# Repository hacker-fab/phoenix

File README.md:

# phoenix

Phoenix is a tube furnace used for thermal oxidation and annealing.

It uses PID control to follow custom temperature profiles and works on both MicroPython on the ESP32 and a simulated Python desktop environment.

<table>
  <tr>
    <td>
      <br>
      <sub>Fig 1. Tube furnace in action</sub>
    </td>
    <td>
      <br>
      <sub>Fig 2. Simulated PID following a heat profile</sub>
    </td>
    <td>
      <br>
      <sub>Fig 3. Controlling ramp rate to prevent thermal shock</sub>
    </td>
  </tr>
</table>

# Python setup
```bash
python3 -m venv .venv
source .venv/bin/activate
pip install -r requirements.txt
```

# Micropython setup

Install micropython
```bash
https://github.com/micropython/micropython/tree/master/ports/unix#readme
```

Install `typing`
```bash
micropython -m mip install github:josverl/micropython-stubs/mip/typing.mpy
```

Install `udataclasses`
```bash
cd ~/.micropython/lib
# extract src/udataclasses
git clone https://github.com/dhrosa/udataclasses.git tmp
mv tmp/src/udataclasses .
rm -rf tmp
```

# Flash code
```
esptool erase-flash
esptool --baud 460800 write-flash 0 images/ESP32_GENERIC_S3-SPIRAM_OCT-20250809-v1.26.0.bin

mpremote
mpremote connect /dev/ttyUSB0 fs cp main.py :
```
- use the UART port (left side) for flashing
- use the USB port (right side) when using mpremote

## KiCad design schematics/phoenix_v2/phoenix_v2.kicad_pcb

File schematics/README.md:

Reverse engineered schematic based on the code from ProjectsInFlight

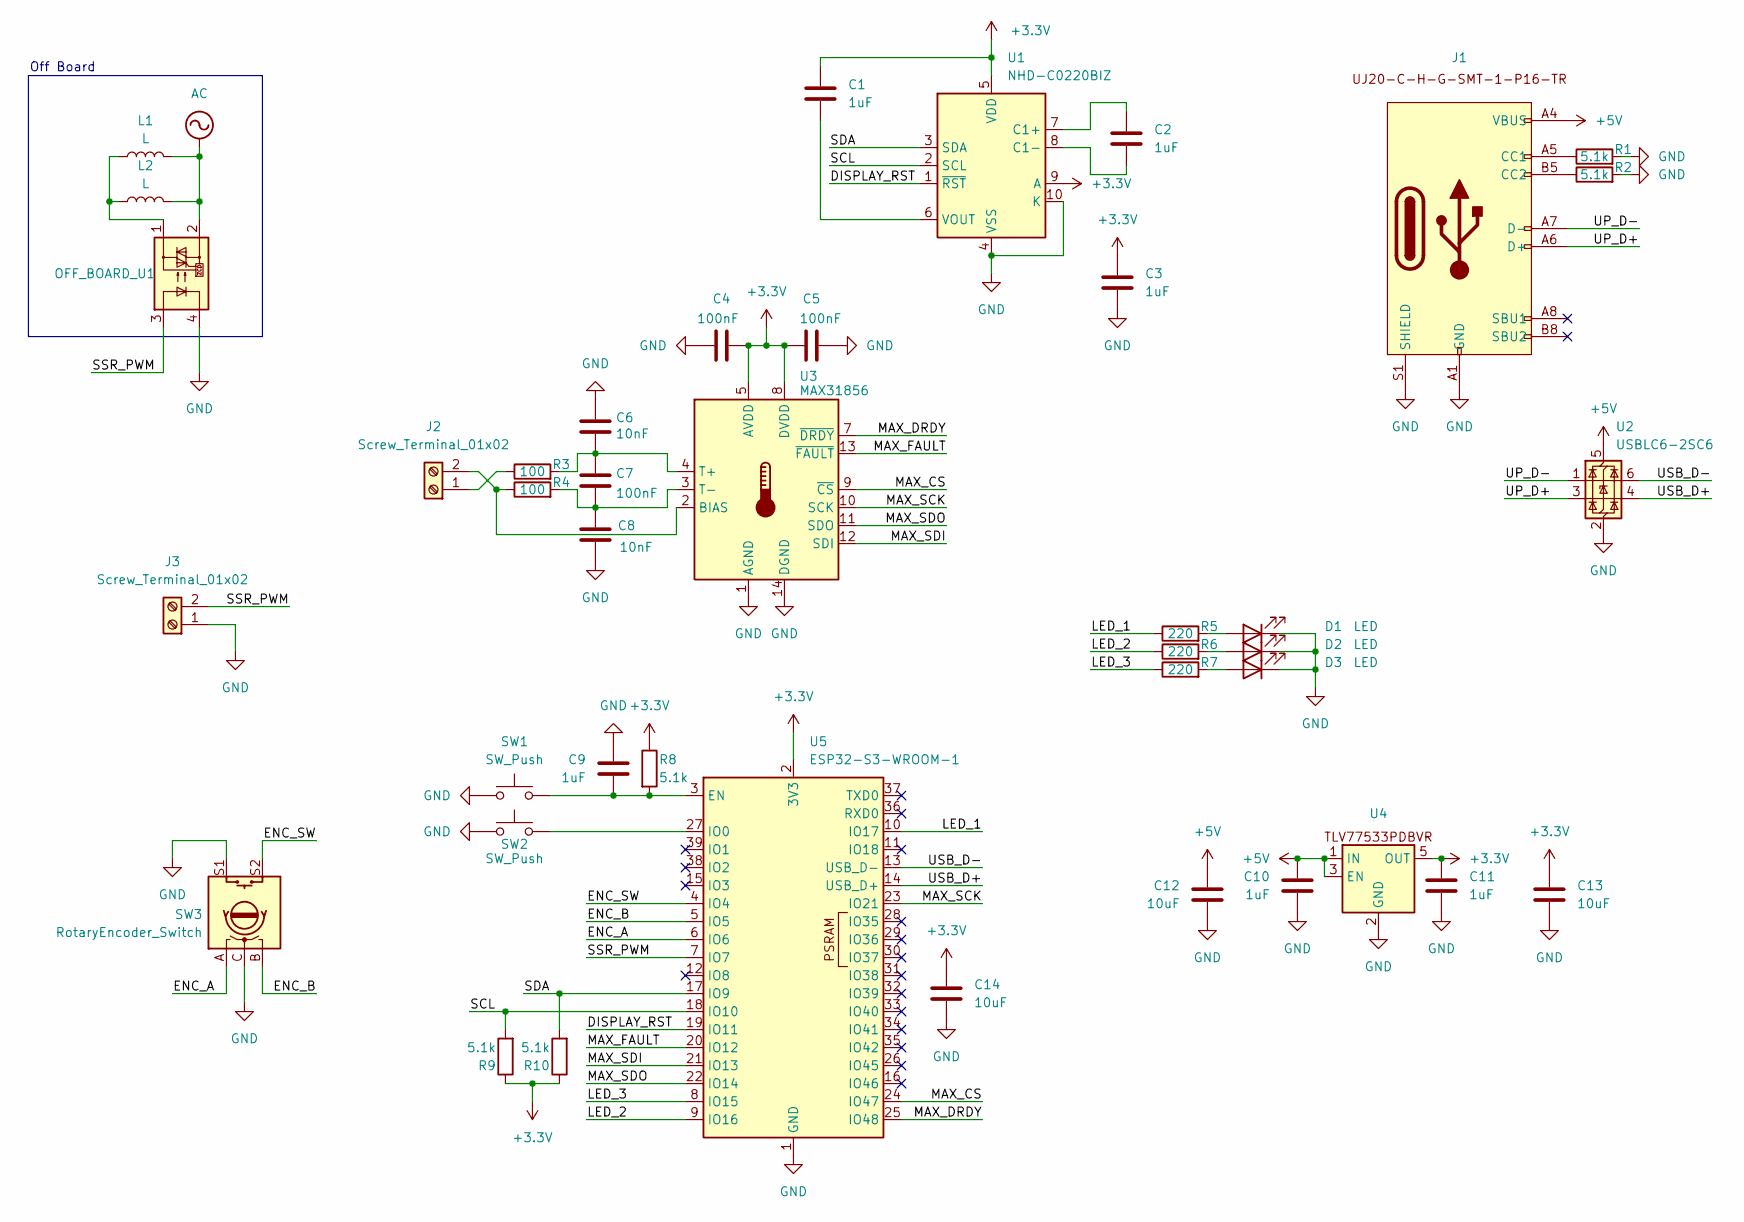
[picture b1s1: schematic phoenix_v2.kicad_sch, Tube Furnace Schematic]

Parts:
C1, C2, C3, C9, C10, C11: 1uF; C_0805_2012Metric
C4, C5, C7: 100nF; C_0805_2012Metric
C6, C8: 10nF; C_0805_2012Metric
C12, C13, C14: 10uF; C_1206_3216Metric_Pad1.33x1.80mm_HandSolder
D1, D2, D3: LED; D_0805_2012Metric_Pad1.15x1.40mm_HandSolder
J1: UJ20-C-H-G-SMT-1-P16-TR
J2, J3: Screw_Terminal_01x02; TE_282837-2
L1, L2: L
OFF_BOARD_U1: (no value)
R1, R2, R8, R9, R10: 5.1k; R_0805_2012Metric_Pad1.20x1.40mm_HandSolder
R3, R4: 100; R_0805_2012Metric_Pad1.20x1.40mm_HandSolder
R5, R6, R7: 220; R_0805_2012Metric_Pad1.20x1.40mm_HandSolder
SW1, SW2: SW_Push; SW_TH_Tactile_Omron_B3F-102x
SW3: RotaryEncoder_Switch; PEC164120FS0012
U1: NHD-C0220BIZ; NHD-C0220BiZ
U2: USBLC6-2SC6; SOT-23-6
U3: MAX31856; TSSOP-14_4.4x5mm_P0.65mm
U4: SOT-23-5
U5: ESP32-S3-WROOM-1

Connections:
+3.3V: C1.1, C3.1, C4.2, C5.1, C11.1, C13.1, C14.1, R8.1, R9.1, R10.1, U1.5 (VDD), U1.9 (A), U3.5 (AVDD), U3.8 (DVDD), U4.5 (OUT), U5.2 (3V3)
+5V: C10.1, C12.1, J1.A4 (VBUS), J1.A9 (VBUS), J1.B4 (VBUS), J1.B9 (VBUS), U2.5 (VBUS), U4.1 (IN), U4.3 (EN)
/DISPLAY_RST: U1.1 (~RST), U5.19 (IO11)
/ENC_A: SW3.A, U5.6 (IO6)
/ENC_B: SW3.B, U5.5 (IO5)
/ENC_SW: SW3.S2, U5.4 (IO4)
/LED_1: R5.1, U5.10 (IO17)
/LED_2: R6.1, U5.9 (IO16)
/LED_3: R7.1, U5.8 (IO15)
/MAX_CS: U3.9 (~CS), U5.24 (IO47)
/MAX_DRDY: U3.7 (~DRDY), U5.25 (IO48)
/MAX_FAULT: U3.13 (~FAULT), U5.20 (IO12)
/MAX_SCK: U3.10 (SCK), U5.23 (IO21)
/MAX_SDI: U3.12 (SDI), U5.21 (IO13)
/MAX_SDO: U3.11 (SDO), U5.22 (IO14)
/SCL: R9.2, U1.2 (SCL), U5.18 (IO10)
/SDA: R10.2, U1.3 (SDA), U5.17 (IO9)
/SSR_PWM: J3.2, OFF_BOARD_U1.3, U5.7 (IO7)
/UP_D+: J1.A6 (D+), J1.B6 (D+), U2.3 (I/O2)
/UP_D-: J1.A7 (D-), J1.B7 (D-), U2.1 (I/O1)
/USB_D+: U2.4 (I/O2), U5.14 (USB_D+)
/USB_D-: U2.6 (I/O1), U5.13 (USB_D-)
GND: C3.2, C4.1, C5.2, C6.1, C8.2, C9.1, C10.2, C11.2, C12.2, C13.2, C14.2, D1.1 (K), D2.1 (K), D3.1 (K), J1.A1 (GND), J1.A12 (GND), J1.B1 (GND), J1.B12 (GND), J1.S1 (SHIELD), J3.1, OFF_BOARD_U1.4, R1.2, R2.2, SW1.1, SW2.1, SW3.C, SW3.S1, U1.4 (VSS), U1.10 (K), U2.2 (GND), U3.1 (AGND), U3.14 (DGND), U4.2 (GND), U4.4 (NC), U5.1 (GND), U5.40 (GND), U5.41 (GND)
unnamed: D1.2 (A), R5.2
unnamed: D2.2 (A), R6.2
unnamed: D3.2 (A), R7.2
unnamed: J1.A5 (CC1), R1.1
unnamed: J1.B5 (CC2), R2.1
unnamed: J2.1, R3.1
unnamed: J2.2, R4.1, U3.2 (BIAS)
unnamed: L1.1, L2.1, OFF_BOARD_U1.1
unnamed: L1.2, L2.2, OFF_BOARD_U1.2
unnamed: C2.1, U1.7 (C1+)
unnamed: C2.2, U1.8 (C1-)
unnamed: C1.2, U1.6 (VOUT)
unnamed: C6.2, C7.1, R3.2, U3.4 (T+)
unnamed: C7.2, C8.1, R4.2, U3.3 (T-)
unnamed: C9.2, R8.2, SW1.2, U5.3 (EN)
unnamed: SW2.2, U5.27 (IO0)

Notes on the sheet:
Off Board

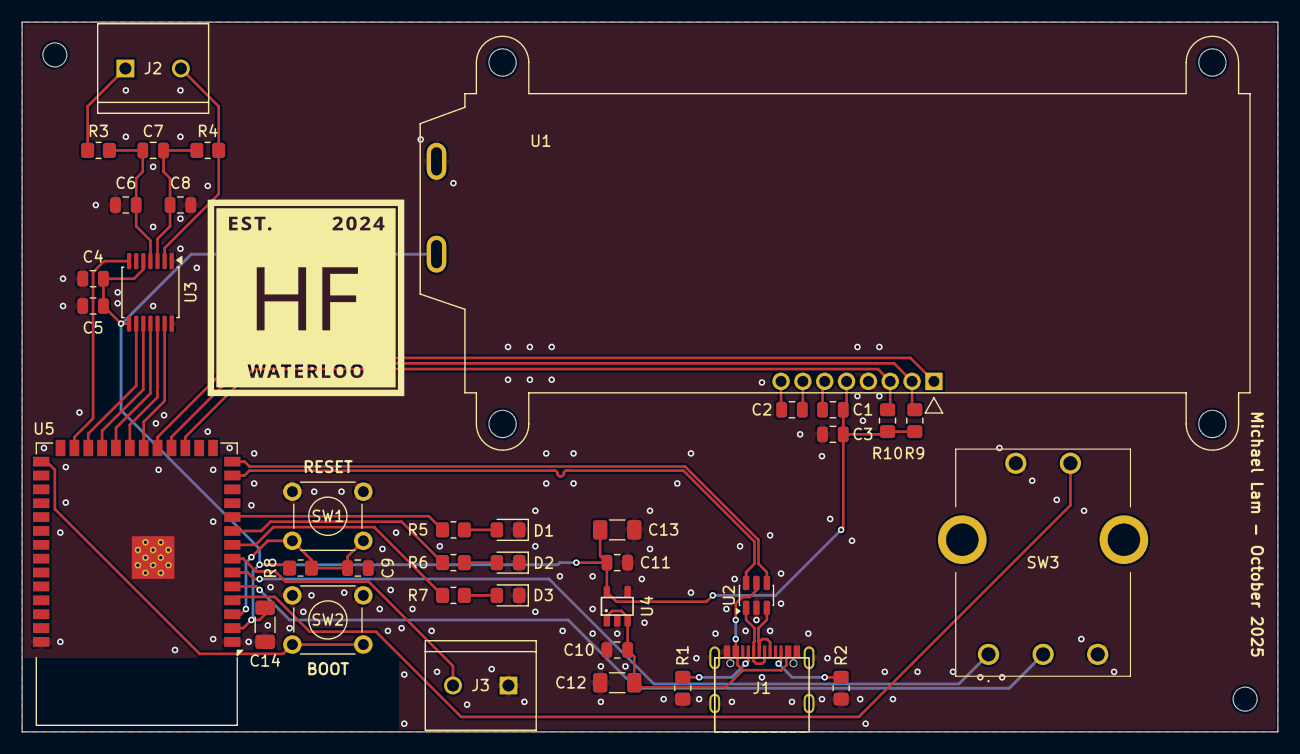
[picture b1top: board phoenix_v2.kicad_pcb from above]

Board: 2 copper layers, 115.0 x 65.0 mm, 38 parts (0 on the bottom side), 37 nets.

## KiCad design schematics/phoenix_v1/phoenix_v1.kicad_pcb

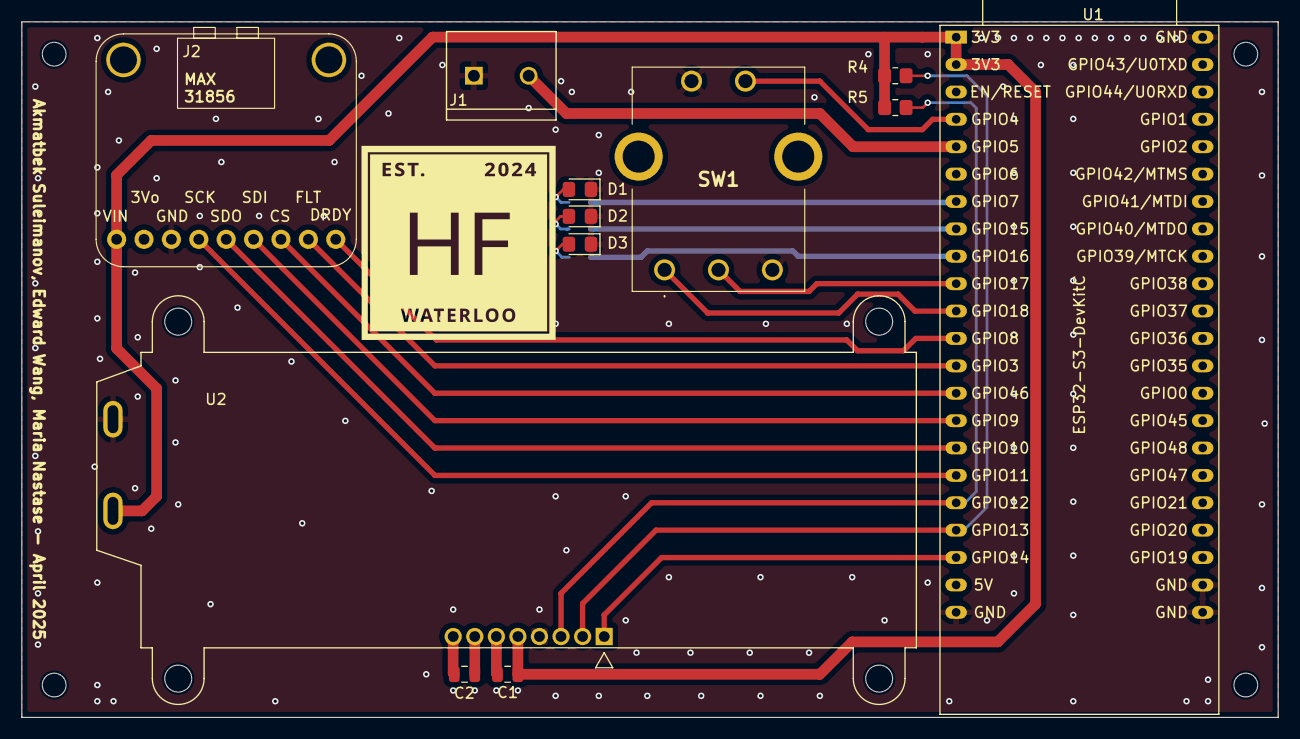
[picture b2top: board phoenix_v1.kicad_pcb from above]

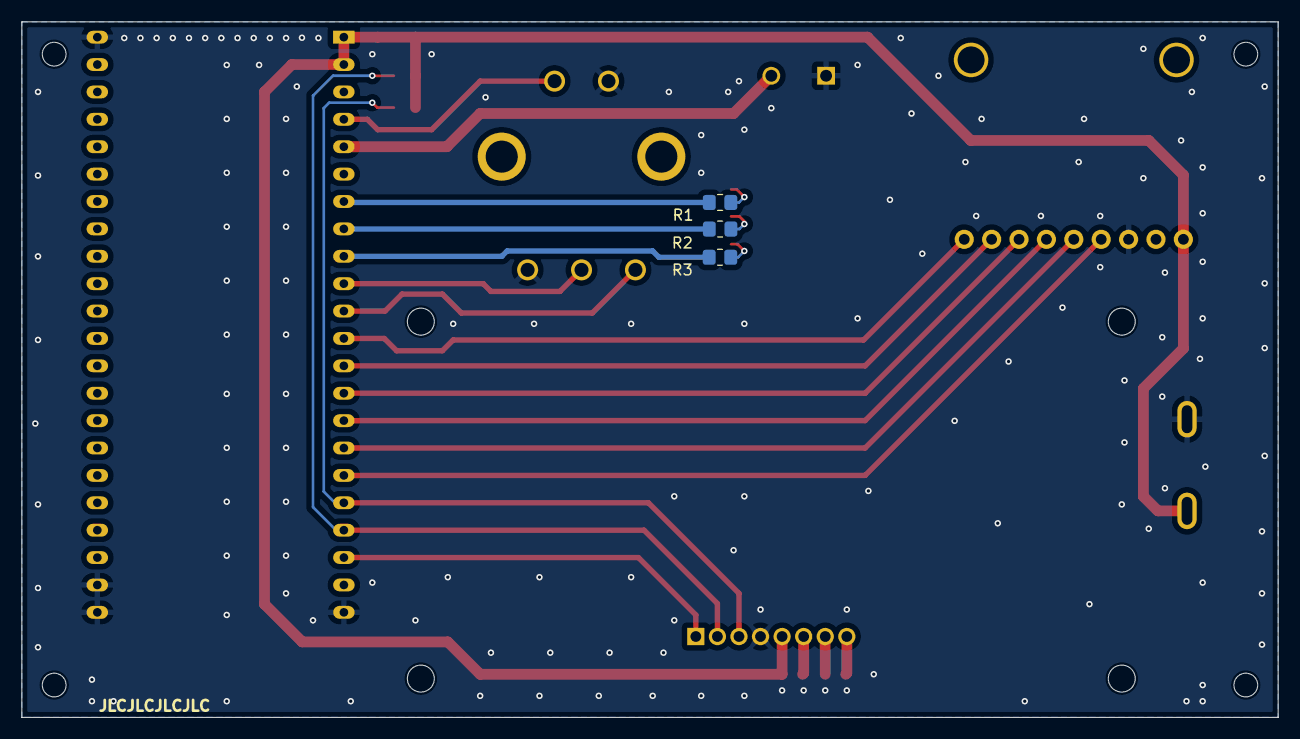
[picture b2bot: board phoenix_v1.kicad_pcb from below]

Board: 2 copper layers, 116.5 x 64.5 mm, 15 parts (3 on the bottom side), 24 nets.

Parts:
C1, C2: 1uF; C_0805_2012Metric
D1, D2, D3: LED; D_0805_2012Metric_Pad1.15x1.40mm_HandSolder
J1: Screw_Terminal_01x02; TE_282837-2
J2: Conn_01x09_Socket; MAX31856_HEADER
R1, R2, R3: 220; R_0805_2012Metric_Pad1.20x1.40mm_HandSolder
R4, R5: 4.7k; R_0805_2012Metric_Pad1.20x1.40mm_HandSolder
SW1: RotaryEncoder_Switch; PEC164120FS0012
U1: ESP32-S3-DevKitC
U2: NHD-C0220BIZ; NHD-C0220BiZ

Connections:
+3.3V: C1.1, J2.9, R4.1, R5.1, U1.1 (3V3), U1.2 (3V3), U2.5 (VDD), U2.9 (A)
/DISPLAY_RST: U1.20 (GPIO14/ADC2_CH3), U2.1 (~RST)
/ENC_A: SW1.A, U1.11 (GPIO18/ADC2_CH7)
/ENC_B: SW1.B, U1.10 (GPIO17/ADC2_CH6)
/ENC_SW: SW1.S2, U1.4 (GPIO4/ADC1_CH3)
/LED_1: R1.1, U1.7 (GPIO7/ADC1_CH6)
/LED_2: R2.1, U1.8 (GPIO15/ADC2_CH4/32K_P)
/LED_3: R3.1, U1.9 (GPIO16/ADC2_CH5/32K_N)
/MAX_CS: J2.3, U1.14 (GPIO46)
/MAX_DRDY: J2.1, U1.12 (GPIO8/ADC1_CH7)
/MAX_FAULT: J2.2, U1.13 (GPIO3/ADC1_CH2)
/MAX_SCK: J2.6, U1.17 (GPIO11/ADC2_CH0)
/MAX_SDI: J2.4, U1.15 (GPIO9/ADC1_CH8)
/MAX_SDO: J2.5, U1.16 (GPIO10/ADC1_CH9)
/SCL: R4.2, U1.19 (GPIO13/ADC2_CH2), U2.2 (SCL)
/SDA: R5.2, U1.18 (GPIO12/ADC2_CH1), U2.3 (SDA)
/SSR_PWM: J1.2, U1.5 (GPIO5/ADC1_CH4)
GND: D1.1 (K), D2.1 (K), D3.1 (K), J1.1, J2.7, SW1.C, SW1.S1, U1.22 (GND), U1.23 (GND), U1.24 (GND), U1.44 (GND), U2.4 (VSS), U2.10 (K)
unnamed: D1.2 (A), R1.2
unnamed: D2.2 (A), R2.2
unnamed: D3.2 (A), R3.2
unnamed: C2.1, U2.7 (C1+)
unnamed: C2.2, U2.8 (C1-)
unnamed: C1.2, U2.6 (VOUT)

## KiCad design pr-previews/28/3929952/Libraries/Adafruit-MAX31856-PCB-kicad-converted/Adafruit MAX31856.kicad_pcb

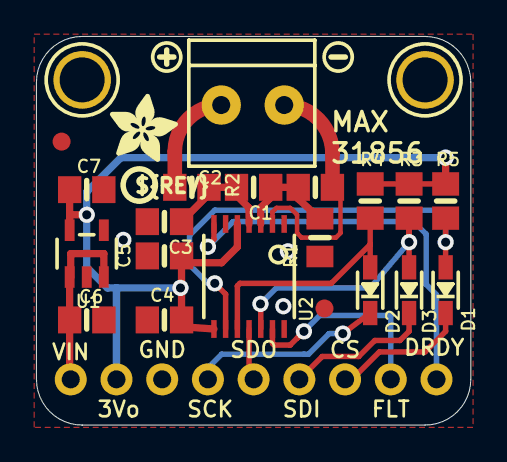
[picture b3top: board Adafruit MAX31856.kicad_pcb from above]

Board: 2 copper layers, 24.1 x 21.6 mm, 28 parts (1 on the bottom side), 16 nets.

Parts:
C1: 0.01uF; 0805_10MGAP
C2, C4, C5: 0.1uF; 0805-NO
C3: 0.01uF; 0805-NO
C6, C7: 10uF; 0805-NO
D1, D2, D3: 1N4148; SOD-323
FID1, FID2: FIDUCIAL""; FIDUCIAL_1MM
JP1: 1X09_ROUND_70
R1, R2: 100; 0805-NO
R3, R4, R5: 10K; 0805-NO
U1: mic5225-3.3; SOT23-5
U2: MAX31856; TSSOP14
U$1: PCBFEAT-REV-040
U$13, U$14: MOUNTINGHOLE2.5; MOUNTINGHOLE_2.5_PLATED
U$23: SYMBOL_PLUS
U$24: SYMBOL_MINUS
U$25: ADAFRUIT_3.5MM
U$26: ADAFRUIT_TEXT_20MM
X1: 3.5mm term; TERMBLOCK_1X2-3.5MM

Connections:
3.3V: C4.1, C5.1, C7.1, JP1.8, R3.2, R4.2, R5.2, U1.5, U2.5, U2.8
DRDY: JP1.1, U2.7
GND: C1.1, C3.2, C4.2, C5.2, C6.2, C7.2, JP1.7, U1.2, U2.1, U2.14
SCK: D2.C, JP1.6
SCK_3V: D2.A, R4.1, U2.10
SDI: D3.C, JP1.4
SDO: JP1.5, U2.11
SDO_3V: D3.A, R3.1, U2.12
T+: C2.2, C3.1, R2.2, U2.4
T-: C1.2, C2.1, R1.2, U2.3
THERM+: R2.1, X1.1
THERM-: R1.1, U2.2, X1.2
VIN: C6.1, JP1.9, U1.1, U1.3
~CS_3V: D1.A, R5.1, U2.9
~CS: D1.C, JP1.3
~FAULT: JP1.2, U2.13

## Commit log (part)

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2025-02-05 upload
2025-02-05 rename src -> TubeFurnace
2025-02-05 installation guide
2025-02-05 formatting
2025-02-05 Revert "formatting"
    This reverts commit 083058cc252f3819b7a6246fb17b9b03613ff680.
2025-02-05 Update LICENSE
2025-02-05 test
2025-02-05 matrix and ls
2025-02-05 fix path
2025-02-05 fix path 2
2025-02-05 install avr
2025-02-05 update index
2025-02-05 cleanup chatgpt comments
2025-02-05 cleanup job name
2025-02-05 build in ci (#3)
    * test
    * matrix and ls
    * fix path
    * fix path 2
    * install avr
    * update index
2025-02-05 .clang-format
2025-02-05 autoformat
2025-02-05 run in ci
2025-02-05 Revert "run in ci"
    This reverts commit 9e731130f4431728779fc97e86db32f08336ba59.
2025-02-05 don't redeclare injected function headers
2025-02-05 autoformat (#4)
    * .clang-format
    * autoformat
    * run in ci
    * Revert "run in ci"
    This reverts commit 9e731130f4431728779fc97e86db32f08336ba59.
    * don't redeclare injected function headers
2025-02-05 lint job
2025-02-05 only needs to run on ubuntu
2025-02-05 linter (#5)
    * run in ci
    * lint job
    * only needs to run on ubuntu
2025-02-05 update readme (#6)
2025-02-05 make linter able to fail
2025-02-05 test with bad indentation
2025-02-05 Revert "test with bad indentation"
    This reverts commit 8122fc583a4bc7f4e7ee4da30116c309f4d25178.
2025-02-05 make linter able to fail (#9)
    * make linter able to fail
    * test with bad indentation
    * Revert "test with bad indentation"
    This reverts commit 8122fc583a4bc7f4e7ee4da30116c309f4d25178.
2025-02-08 move tests to seperate folders
2025-02-08 move tests to seperate folders (#10)
2025-02-08 move tests to root
2025-02-27 relay test script
2025-02-27 relay test script (#12)
2025-02-27 gitignore
2025-02-27 rename to v0
2025-02-27 rename kicad project to v0 (#13)
    * gitignore
    * rename to v0
2025-03-01 add esp32 libraries
2025-03-07 v1 schematic
2025-03-08 update for esp32
2025-03-08 screw terminal
2025-03-08 comment
2025-03-08 update test_thermocouple for esp32 (#16)
    * update for esp32
    * comment
2025-03-10 update screnshot
2025-03-10 v1 schematic (#14)
    * v1 schematic
    * screw terminal
    * update screnshot
    ---------
2025-03-10 layout
2025-03-10 fix duplicate
2025-03-10 max31856 socket
2025-03-11 add ncs
2025-03-17 upload screw terminal files
2025-03-17 footprint assignment
2025-03-17 upload MAX31856 eagle-converted source
2025-03-17 create custom footprint for MAX31856 header
2025-03-19 upload pec stuff
2025-03-19 use project footprint library
2025-03-21 extract PEC footprint and sym
2025-03-21 finish assigning footprints and update PCB
2025-03-21 assign footprints (#17)
    * layout
    * fix duplicate
    * max31856 socket
    * add ncs
    * upload screw terminal files
    * footprint assignment
2025-03-21 exclude relay and inductors from board
2025-03-21 exclude relay and inductors from board (#18)
2025-03-21 set R for leds
2025-03-21 set R for leds (#19)
2025-03-21 reannotate
2025-03-21 reannotate (#20)
2025-03-21 caps for display (#21)
2025-03-21 first try
2025-03-21 upload pages v3
2025-03-21 better title
2025-03-21 try kiri instead
2025-03-21 checkout v4?
2025-03-21 reddragon version
2025-03-21 try branch
2025-03-21 use fork with upload v4
2025-03-21 random diff to trigger run
2025-03-21 try overall checkout v2
2025-03-21 go back
2025-03-21 initial nojekyll
2025-03-21 retrigger
2025-03-21 correct .kicad_pro path
2025-03-21 v1.2
2025-03-21 random edit to trigger
2025-03-21 make a .kiri folder and trigger
2025-03-21 more trigger
2025-03-21 perms
2025-03-21 Update Kiri output for PR #23
2025-03-21 pr perm
2025-03-21 try gitkeep?
2025-03-21 try different path and pwd
2025-03-21 USE THE ENV VAR CORRECTLY!!!!!!!!!!!
2025-03-21 revert sch
2025-03-21 v1.2.1
2025-03-21 v1.2.2
2025-03-21 v.1.2.3
2025-03-21 v.1.2.4
2025-03-21 kiri setup (#23)
    * first try
    * upload pages v3
    * better title
    * try kiri instead
    * checkout v4?
    * reddragon version
2025-03-21 trigger
2025-03-21 output dir
2025-03-21 try fix output dir
2025-03-21 no output dir
2025-03-21 v.1.2.5
2025-03-21 v.1.2.6
2025-03-21 v.1.2.7
2025-03-21 v1.2.8
2025-03-21 v1.2.9
2025-03-21 v1.2.10
2025-03-21 v1.2.11
2025-03-21 v1.2.12
2025-03-21 revert move
2025-03-21 Revert "revert move"
    This reverts commit c8a7fecc3ba229a40b8fc048a70462a0a6fe9e72.
2025-03-21 Revert "Revert "revert move""
    This reverts commit a785919d6cb81062de9690204b0b46e338bb406e.
2025-03-21 v.1.2.13
2025-03-21 v1.2.14
2025-03-21 Revert "Revert "Revert "revert move"""
    This reverts commit 077da6f8a26816faf5dd7f152d1a63141e9c7252.
2025-03-21 github-pages env
2025-03-21 Revert "Revert "Revert "Revert "revert move""""
    This reverts commit 9c1976028def966c5564fcd19b8b1fd2f330ae00.
2025-03-21 v1.2.15
2025-03-21 Revert "Revert "Revert "Revert "Revert "revert move"""""
    This reverts commit ef8d35f938a2ff7061ca819bc9f4d280fc4012b7.
2025-03-21 v1.2.17
2025-03-21 v1.2.18
2025-03-21 Revert "Revert "Revert "Revert "Revert "Revert "revert move""""""
    This reverts commit e7fcf7812303bad959b3ae7c36b8afc2bb990449.
2025-03-21 Revert "Revert "Revert "Revert "Revert "Revert "Revert "revert move"""""""
    This reverts commit 42d8571e8d9c44e463d96eba7e5713493cb319a8.
2025-03-22 show which direction MAX is facing
2025-03-22 arrange and draw outline
2025-03-22 Update Kiri output for PR #25
2025-03-22 better alignment
2025-03-22 arrange stuff and draw outline (#25)
    * show which direction MAX is facing
    * arrange and draw outline
    * better alignment
    ---------
2025-03-22 fix encoder footprint and label mismatch
2025-03-22 Update Kiri output for PR #26
2025-03-22 update on pcb
2025-03-22 fix max footprint (#27)
    * delete extra stuff on max breakout footprint
    * update on pcb
    ---------
2025-03-22 make board outline silkscreen instead of edgecuts
2025-03-22 some wiring
2025-03-22 update pcb for max footprint
2025-03-22 cleanup max header
2025-03-22 route everything and GND fill and via stitch
2025-03-22 Update Kiri output for PR #28
2025-03-26 v2.0.2
2025-03-26 tiny change to trigger diff
2025-03-26 environment: github pages
2025-03-26 another small diff
2025-03-26 v2.0.3
2025-03-26 v2.0.4
2025-03-26 v2.0.5
2025-03-26 Update Kiri output for PR #29
2025-03-26 kiri action on gh-pages classic (#29)
    * v2.0.2
    * tiny change to trigger diff
    * environment: github pages
    * another small diff
    * v2.0.3
    * v2.0.4
2025-03-26 title blocks
2025-03-26 export pdfs
2025-04-12 fix "Dont mix global and local net labels for the same net (SSR_PWM)"
2025-04-12 fix "it should be made clear on the schematic that U1 and surrounding components are off board"
2025-04-12 fix "NHD-CO22BIZ needs 3.3V not 5V"
2025-04-12 connect A and K on lcd
2025-04-12 fix "routing for the I2C pullups VDD trace"
2025-04-12 fix "more space on display mounting holes"
2025-04-12 upload DRU
2025-04-12 fix new DRC errors
2025-04-12 more vias
2025-04-12 zip gerber script
2025-04-12 generate GERB
2025-04-12 update zip script for new path
2025-04-13 HF log!!!!!!!!
2025-04-13 hf logo as footprint
2025-04-13 update gerb
2025-04-13 add names and mounting holes
2025-04-13 fix J1 missing
2025-04-15 routing (#28)
    * make board outline silkscreen instead of edgecuts
    * some wiring
    * update pcb for max footprint
    * cleanup max header
    * route everything and GND fill and via stitch
    * title blocks
2025-04-16 requirements
2025-04-16 chat... gpt...
2025-04-16 improvement
2025-04-16 python gitignore
2025-04-16 req.txt
2025-04-16 split out running_average
2025-04-16 test_running_average.py
2025-04-16 split out pid.py and sim.py
2025-04-16 rename RampSoakPID -> RampSoak
2025-04-16 rename HeatSimConfig -> ThermalModel
2025-04-16 rename py/ -> python/
2025-04-16 ruff
2025-04-16 test_sim.py
2025-04-16 more realistic thermal params and plot better
2025-04-16 make to_pwm output in [0.0, 1.0]
2025-04-16 more realistic convergence and parametrize rate limit
2025-04-16 rewrite pid in python (#34)
    * requirements
    * chat... gpt...
    * improvement
    * python gitignore
    * req.txt
    * split out running_average
2025-04-16 ruff in ci
2025-04-16 better name
2025-04-16 140 line length
2025-04-16 autoformat script
2025-04-16 ruff in ci (#35)
    * ruff in ci
    * better name
    * 140 line length
    * autoformat script
    * autoformat
    * better name
2025-04-16 run pytest
2025-04-16 only run kiri when schematics/* is changed
2025-04-16 run pytest in ci (#36)
2025-04-16 only run kiri when schematics/* is changed (#37)
2025-04-16 graphs
2025-04-16 use heat profile
2025-04-16 test profile
2025-04-16 validate profile test
2025-04-18 follow heat curve (#39)
    * use heat profile
    * autoformat
    * test profile
    * validate profile test
    * autoformat
2025-04-18 calculate slope better and plot
2025-04-18 plotting
2025-04-18 gitignore graphs
2025-04-18 save to image
2025-04-18 delete sim.py and fix test_sim (#42)
    * delete sim.py and rename sim_profile.py to sim.py
    * calculate slope better and plot
    * plotting
    * gitignore graphs
    * save to image
2025-04-19 readme
2025-04-19 add conditional import for udataclasses
2025-04-19 small script to test micropy
2025-04-19 compute convergence over all setpoints
2025-04-19 venv
2025-04-19 readme (#43)
    * readme
    * venv
2025-04-19 compute convergence over all setpoints (#46)
2025-04-19 micropython port (#44)
    * add conditional import for udataclasses
    * small script to test micropy
2025-04-19 fix kiri paths
2025-04-19 fix kiri "no jobs were run" (#47)
2025-09-08 install instructions
2025-09-08 update workflows
2025-09-08 fix paths
2025-09-08 fix paths 2
2025-09-08 move ino scripts to scripts/examples/
2025-09-08 only test when real files have changed
2025-09-08 cleanup (#49)
    * delete arduino stuff
    * update workflows
    * fix paths
    * fix paths 2
    * move ino scripts to scripts/examples/
    * only test when real files have changed
2025-09-08 try out leds
2025-09-08 fix formatting
2025-09-09 rename stuff, add lcd.c and got lcd.py scan() working
2025-09-10 found docs on Co and RS
2025-09-10 try running my thing and also a chat gpt attempt
2025-09-16 [encoder] Implement Rotary Encoder driver with interrupts (on esp32-s3-devkitm-1)
2025-09-19 feat: initial implementation for curve editor
2025-09-20 feat: undo and redo system
2025-09-20 type hints and cleanup
2025-09-20 fix dragging points past each other
2025-09-20 add help bar on bottom
2025-09-20 cleanups
2025-09-20 more progess, styling, added points table
2025-09-20 more columns on sidebar info
2025-09-20 move curve editor, update requirements
2025-09-22 refactor scripts.py
2025-09-22 start writing hw examples in scripts/ (#50)
    * try out leds
    * fix formatting
    * rename stuff, add lcd.c and got lcd.py scan() working
    * wip
    * found docs on Co and RS
    * try running my thing and also a chat gpt attempt
2025-09-22 update pin mappings for real HW
2025-09-22 Implement Rotary Encoder driver with interrupts (#52)
    * [encoder] Implement Rotary Encoder driver with interrupts (on esp32-s3-devkitm-1)
    * update pin mappings for real HW
    ---------
2025-09-22 make it work!
2025-09-22 rename
2025-09-22 cleanup
2025-09-22 better style
2025-09-22 thermocouple bringup (#53)
    * temp
    * make it work!
    * rename
    * cleanup
    * better style
    ---------
2025-09-23 test scrip working
2025-09-23 refactor to class
2025-09-23 BurstFire bringup (#54)
    * test scrip working
    * refactor to class
    ---------
2025-09-23 remove unused functions
2025-09-23 remove debugging code, shorten docstrings
2025-09-28 mpy_main
2025-09-28 clamp pid to [0.0, 1.0]
2025-09-28 mv mpy_main -> main, remove sim from it
2025-09-28 use mpy time module
2025-09-28 adjust heat profile for lower power
2025-09-28 make heat_profile use ms instead of s
2025-10-07 [lcd] Implement I2C driver (ST7036) + test for NHD‑C0220BiZ display
2025-10-09 [lcd] Implement I2C driver (ST7036) + test for NHD‑C0220BiZ display (#55)
2025-10-19 Squash merge assembly into with-display
2025-10-19 UNTESTED: copy display to src, make version that updates display when running heating profile
2025-10-20 Changed decoupling capacitor value for ESP32-S3
2025-10-20 Forgot to change capacitor size
